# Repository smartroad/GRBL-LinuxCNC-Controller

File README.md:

GRBL-LinuxCNC-Controller
========================

Dual purpose controller to work with Arduino GRBL and Parallel port LinuxCNC

This controller is meant to be dual use. It can be used on the Arduino GRBL platform but can also be used with the LinuxCNC software via a parallel port.

It uses 3 Pololu or Stepstick drivers for XYZ steppers.

This hasn't yet been produced or made so it is totally possible that it doesn't work!

The design allows for 3 axis of movement, 3 limit/home switches, spindle activation and direction control.

Along on side there is a row of LEDs, these are connected to the enable, step and dir lines for the stepper drivers. While I could probably justify thier inclusion, honestly? I put them there as I love blinking lights as the machine moves ;)

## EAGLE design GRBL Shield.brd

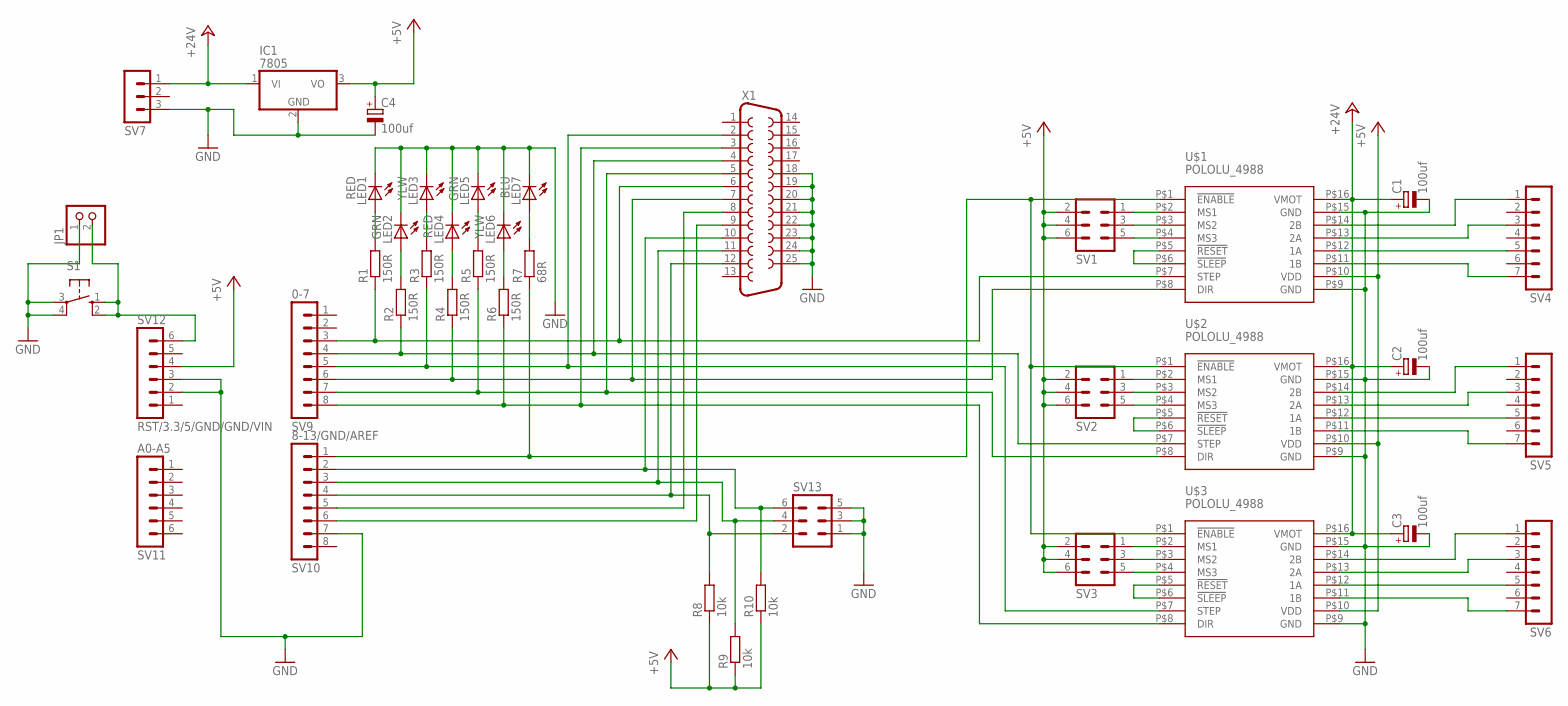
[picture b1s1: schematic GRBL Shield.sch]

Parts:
C1, C2, C3, C4: 100uf; E2,5-7
IC1: 7805; TO220V
JP1: PINHD-1X2; 1X02
LED1, LED4: RED; LED5MM
LED2, LED5: GRN; LED5MM
LED3, LED6: YLW; LED5MM
LED7: BLU; LED5MM
R1, R2, R3, R4, R5, R6: 150R; 0207/2V
R7: 68R; 0207/2V
R8, R9, R10: 10k; 0204/7
S1: 10-XX; B3F-10XX
SV1, SV2, SV3, SV13: MA03-2
SV4, SV5, SV6: MA07-1
SV7: MA03-1
SV9: 0-7; MA08-1
SV10: 8-13/GND/AREF; MA08-1
SV11: A0-A5; MA06-1
SV12: RST/3.3/5/GND/GND/VIN; MA06-1
U$1, U$2, U$3: POLOLU_4988
X1: F25H

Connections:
+5V: C4.+, IC1.3 (VO), R8.1, R9.1, R10.1, SV1.2, SV1.4, SV1.6, SV2.2, SV2.4, SV2.6, SV3.2, SV3.4, SV3.6, SV12.4, U$1.P$10 (VDD), U$2.P$10 (VDD), U$3.P$10 (VDD)
+24V: C1.+, C2.+, C3.+, IC1.1 (VI), SV7.1, U$1.P$16 (VMOT), U$2.P$16 (VMOT), U$3.P$16 (VMOT)
D2: R1.1, SV9.3, U$1.P$7 (STEP), X1.6
D3: R2.1, SV9.4, U$2.P$7 (STEP), X1.4
D4: R3.1, SV9.5, U$3.P$7 (STEP), X1.2
D5: R4.1, SV9.6, U$1.P$8 (DIR), X1.7
D6: R5.1, SV9.7, U$2.P$8 (DIR), X1.5
D7: R6.1, SV9.8, U$3.P$8 (DIR), X1.3
D8: R7.1, SV10.1, U$1.P$1 (!ENABLE), U$2.P$1 (!ENABLE), U$3.P$1 (!ENABLE)
D9: R10.2, SV10.2, SV13.6, X1.10
D10: R9.2, SV10.3, SV13.4, X1.11
D11: R8.2, SV10.4, SV13.2, X1.12
D12: SV10.5, X1.8
D13: SV10.6, X1.9
GND: C1.-, C2.-, C3.-, C4.-, IC1.2 (GND), JP1.1, LED1.K (C), LED2.K (C), LED3.K (C), LED4.K (C), LED5.K (C), LED6.K (C), LED7.K (C), S1.3, S1.4 (P1), SV7.3, SV10.7, SV12.2, SV12.3, SV13.1, SV13.3, SV13.5, U$1.P$9 (GND), U$1.P$15 (GND), U$2.P$9 (GND), U$2.P$15 (GND), U$3.P$9 (GND), U$3.P$15 (GND), X1.18, X1.19, X1.20, X1.21, X1.22, X1.23, X1.24, X1.25
unnamed: U$1.P$5 (!RESET), U$1.P$6 (!SLEEP)
unnamed: U$2.P$5 (!RESET), U$2.P$6 (!SLEEP)
unnamed: U$3.P$5 (!RESET), U$3.P$6 (!SLEEP)
unnamed: SV1.1, U$1.P$2 (MS1)
unnamed: SV1.3, U$1.P$3 (MS2)
unnamed: SV1.5, U$1.P$4 (MS3)
unnamed: SV2.1, U$2.P$2 (MS1)
unnamed: SV2.3, U$2.P$3 (MS2)
unnamed: SV2.5, U$2.P$4 (MS3)
unnamed: SV3.1, U$3.P$2 (MS1)
unnamed: SV3.3, U$3.P$3 (MS2)
unnamed: SV3.5, U$3.P$4 (MS3)
unnamed: SV4.1, U$1.P$14 (2B)
unnamed: SV4.3, U$1.P$13 (2A)
unnamed: SV4.5, U$1.P$12 (1A)
unnamed: SV4.7, U$1.P$11 (1B)
unnamed: SV5.1, U$2.P$14 (2B)
unnamed: SV5.3, U$2.P$13 (2A)
unnamed: SV5.5, U$2.P$12 (1A)
unnamed: SV5.7, U$2.P$11 (1B)
unnamed: SV6.1, U$3.P$14 (2B)
unnamed: SV6.3, U$3.P$13 (2A)
unnamed: SV6.5, U$3.P$12 (1A)
unnamed: SV6.7, U$3.P$11 (1B)
unnamed: LED1.A, R1.2
unnamed: LED2.A, R2.2
unnamed: LED3.A, R3.2
unnamed: LED4.A, R4.2
unnamed: LED5.A, R5.2
unnamed: LED6.A, R6.2
unnamed: LED7.A, R7.2
RESET: JP1.2, S1.1 (S), S1.2 (S1), SV12.6

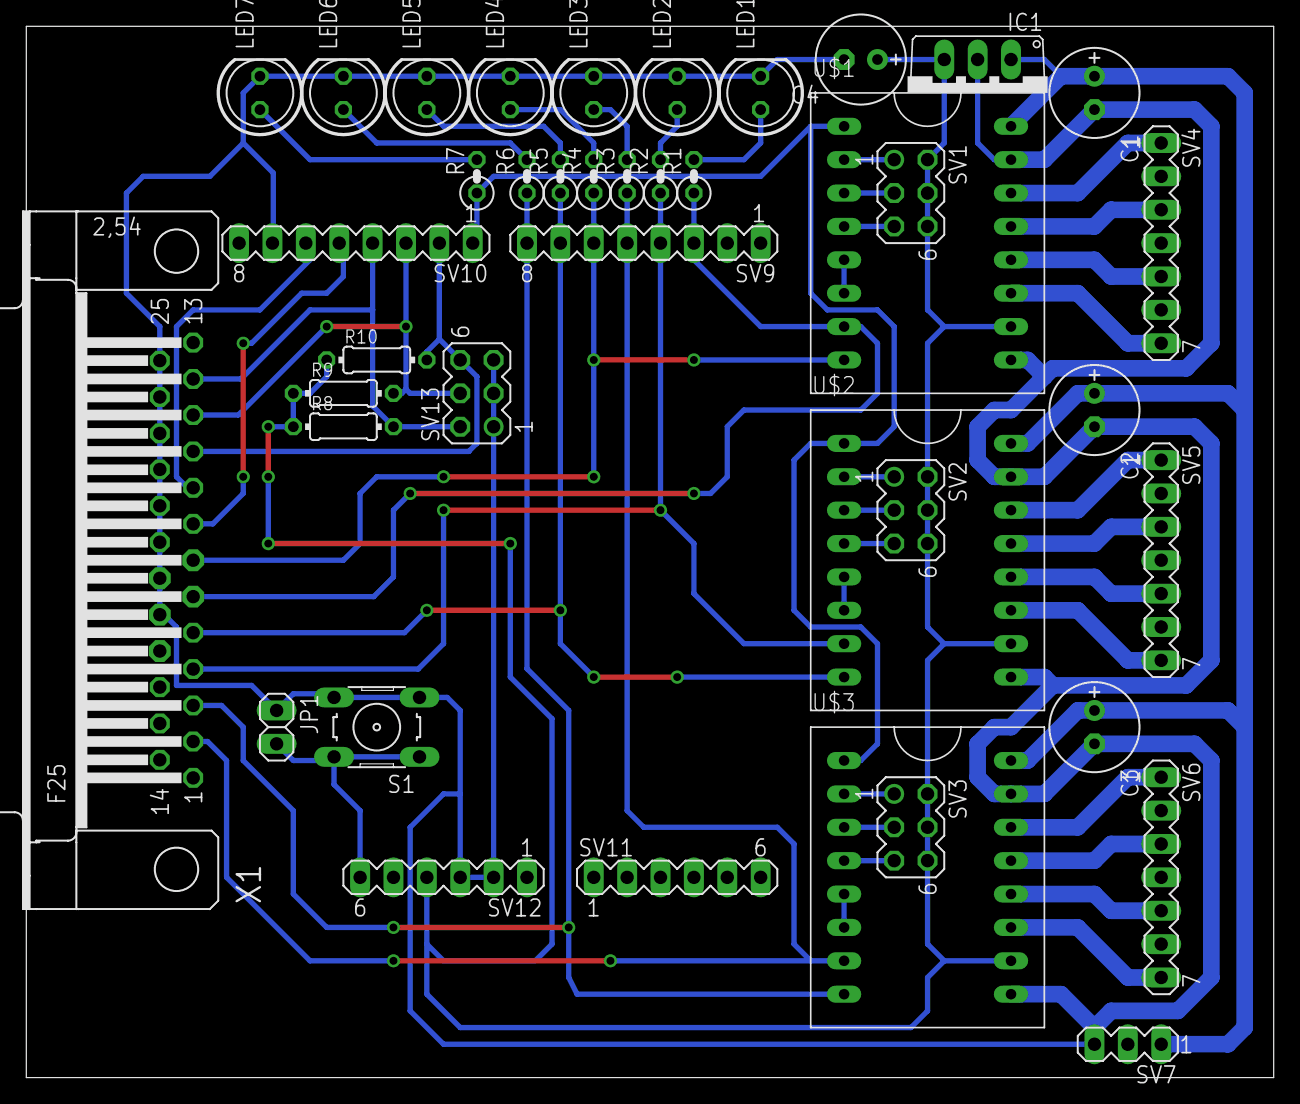
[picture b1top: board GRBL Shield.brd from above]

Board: 2 copper layers, 94.9 x 80.0 mm, 40 parts (0 on the bottom side), 47 nets.

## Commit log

2014-05-28 Circuit Diagram image
2014-05-28 Added values for components and added 5V regulator #1
2014-05-28 Updated diagram to reflect last commit
